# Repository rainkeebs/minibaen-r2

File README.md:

# minibaen
 These files made in KiCad 5.99 (Nightly)
 
 These files are tested but I assume 0 responsibility should something go wrong.
 
 Firmware can be found [here](https://github.com/rainkeebs/vial-qmk/tree/vial/keyboards/minibaen)

Sorry for messy files...

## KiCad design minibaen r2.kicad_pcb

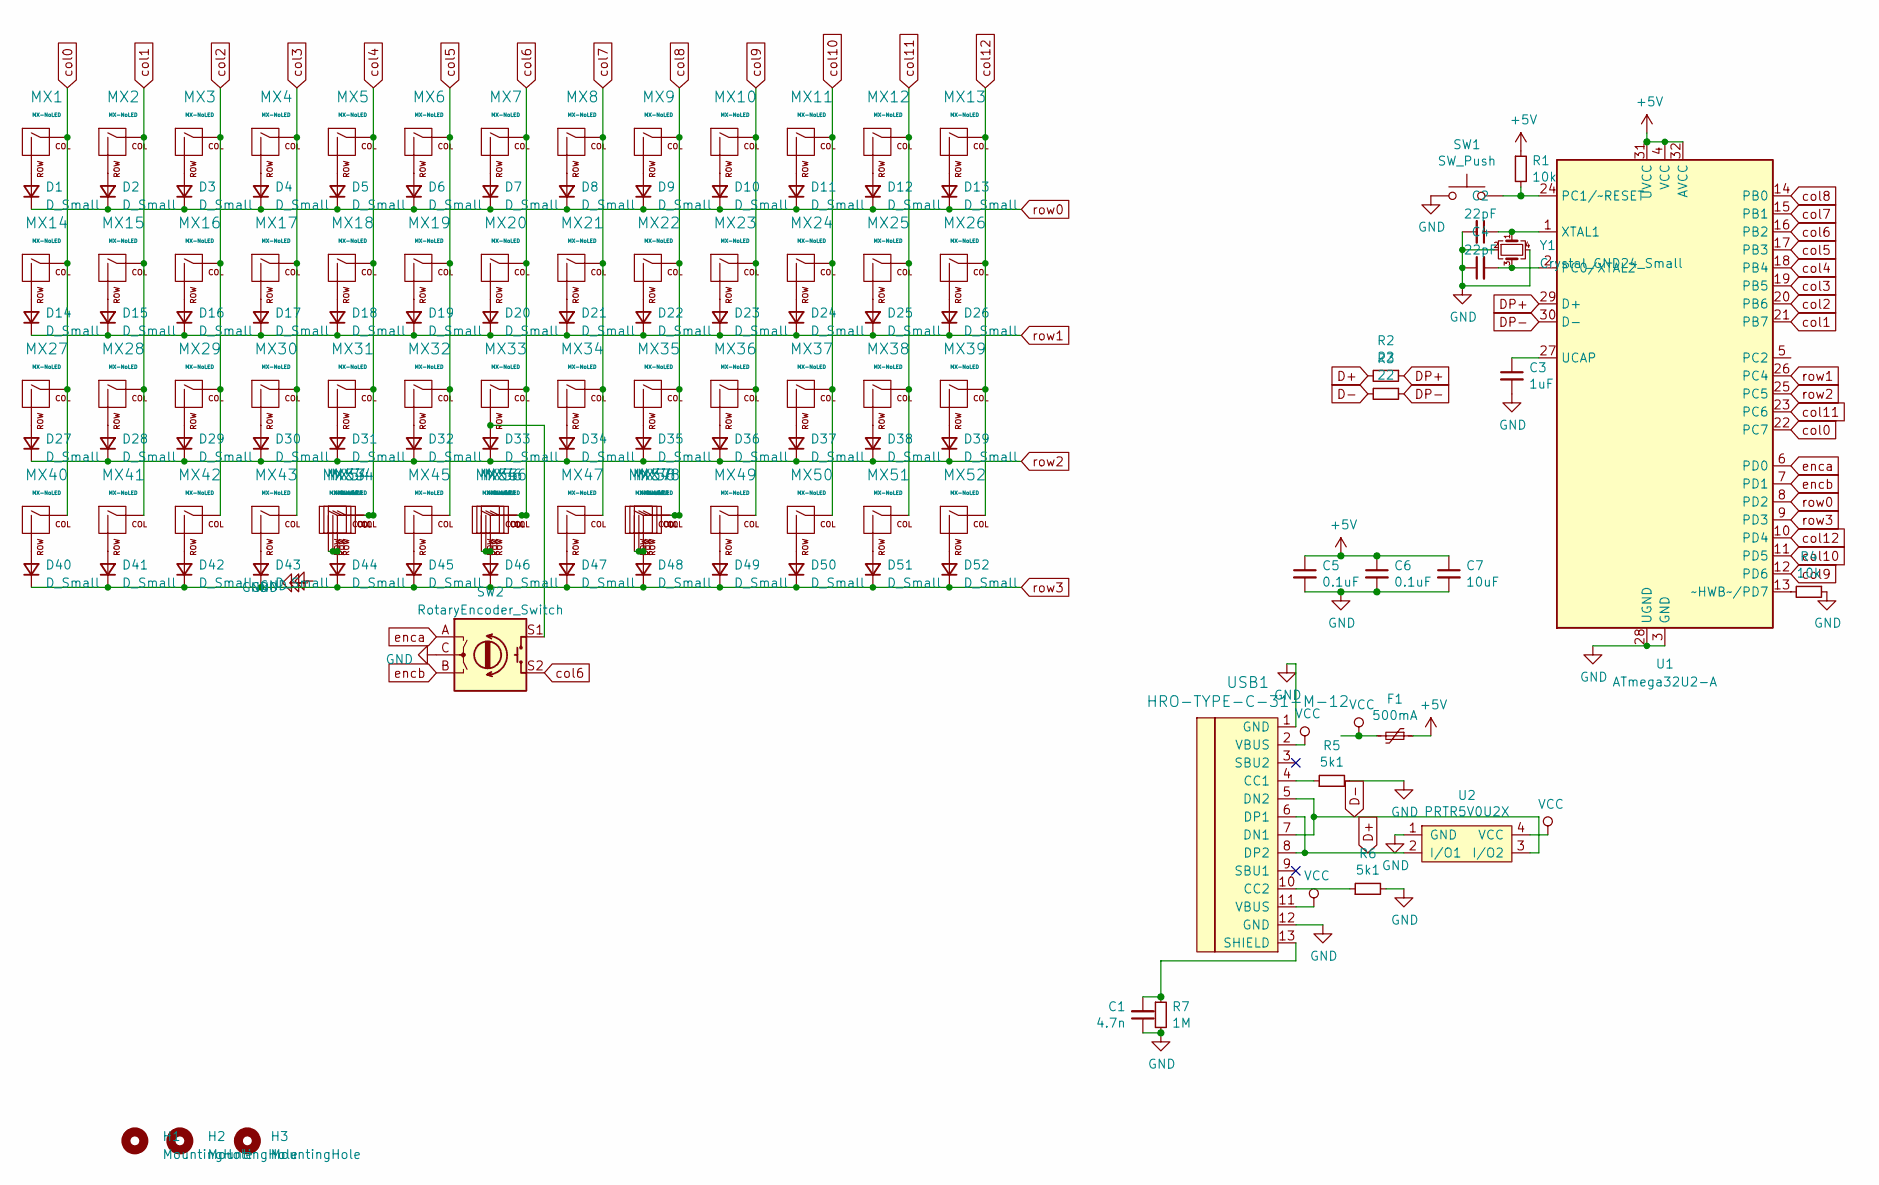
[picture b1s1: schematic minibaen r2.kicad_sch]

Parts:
C1: 4.7n; C_0603_1608Metric
C2, C4: 22pF; C_0603_1608Metric
C3: 1uF; C_0603_1608Metric
C5, C6: 0.1uF; C_0603_1608Metric
C7: 10uF; C_0603_1608Metric
D1, D2, D3, D4, D5, D6, D7, D8, D9, D10, D11, D12, D13, D14, D15, D16, D17, D18, D19, D20, D21, D22, D23, D24, D25, D26, D27, D28, D29, D30, D31, D32, D33, D34, D35, D36, D37, D38, D39, D40, D41, D42, D43, D44, D45, D46, D47, D48, D49, D50, D51, D52: D_Small; D_SOD-123
F1: 500mA; Fuse_1206_3216Metric
H1, H2, H3: MountingHole; MountingHole_2.2mm_M2_DIN965_Pad
MX1, MX2, MX3, MX4, MX5, MX6, MX7, MX8, MX9, MX10, MX11, MX12, MX13, MX14, MX15, MX16, MX17, MX18, MX19, MX20, MX21, MX22, MX23, MX24, MX25, MX26, MX27, MX28, MX29, MX30, MX31, MX32, MX33, MX34, MX35, MX36, MX37, MX38, MX39, MX40, MX41, MX42, MX43, MX44, MX45, MX46, MX47, MX48, MX49, MX50, MX51, MX52: MX-NoLED; MXOnly-1U-NoLED
MX53, MX57: MX-NoLED; MXOnly-2U-ReversedStabilizers-NoLED
MX54, MX56, MX58: MX-NoLED; MXOnly-3U-ReversedStabilizers-NoLED
MX55: MX-NoLED; MXOnly-7U-ReversedStabilizers-NoLED
R1, R4: 10k; R_0603_1608Metric
R2, R3: 22; R_0603_1608Metric
R5, R6: 5k1; R_0603_1608Metric
R7: 1M; R_0603_1608Metric
SW1: SW_Push; PinHeader_1x02_P2.54mm_Vertical
SW2: RotaryEncoder_Switch; RotaryEncoder_EC11-no-legs
U1: ATmega32U2-A; TQFP-32_7x7mm_P0.8mm
U2: PRTR5V0U2X; SOT-143
USB1: HRO-TYPE-C-31-M-12
Y1: Crystal_GND24_Small; Crystal_SMD_3225-4Pin_3.2x2.5mm

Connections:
+5V: C5.1, C6.1, C7.1, F1.1, R1.1, U1.4 (VCC), U1.31 (UVCC), U1.32 (AVCC)
D+: R2.2, U2.2 (I/O1), USB1.6 (DP1), USB1.8 (DP2)
D-: R3.2, U2.3 (I/O2), USB1.5 (DN2), USB1.7 (DN1)
DP+: R2.1, U1.29 (D+)
DP-: R3.1, U1.30 (D-)
GND: C1.1, C2.2, C3.2, C4.1, C5.2, C6.2, C7.2, R4.1, R5.2, R6.2, R7.2, SW1.1, SW2.C, U1.3 (GND), U1.28 (UGND), U2.1 (GND), USB1.1 (GND), USB1.12 (GND), Y1.2, Y1.4
unnamed: C1.2, R7.1, USB1.13 (SHIELD)
unnamed: C2.1, U1.1 (XTAL1), Y1.1
unnamed: C3.1, U1.27 (UCAP)
unnamed: C4.2, U1.2 (PC0/XTAL2), Y1.3
unnamed: D1.2 (A), MX1.2 (ROW)
unnamed: D2.2 (A), MX2.2 (ROW)
unnamed: D3.2 (A), MX3.2 (ROW)
unnamed: D4.2 (A), MX4.2 (ROW)
unnamed: D5.2 (A), MX5.2 (ROW)
unnamed: D6.2 (A), MX6.2 (ROW)
unnamed: D7.2 (A), MX7.2 (ROW)
unnamed: D8.2 (A), MX8.2 (ROW)
unnamed: D9.2 (A), MX9.2 (ROW)
unnamed: D10.2 (A), MX10.2 (ROW)
unnamed: D11.2 (A), MX11.2 (ROW)
unnamed: D12.2 (A), MX12.2 (ROW)
unnamed: D13.2 (A), MX13.2 (ROW)
unnamed: D14.2 (A), MX14.2 (ROW)
unnamed: D15.2 (A), MX15.2 (ROW)
unnamed: D16.2 (A), MX16.2 (ROW)
unnamed: D17.2 (A), MX17.2 (ROW)
unnamed: D18.2 (A), MX18.2 (ROW)
unnamed: D19.2 (A), MX19.2 (ROW)
unnamed: D20.2 (A), MX20.2 (ROW)
unnamed: D21.2 (A), MX21.2 (ROW)
unnamed: D22.2 (A), MX22.2 (ROW)
unnamed: D23.2 (A), MX23.2 (ROW)
unnamed: D24.2 (A), MX24.2 (ROW)
unnamed: D25.2 (A), MX25.2 (ROW)
unnamed: D26.2 (A), MX26.2 (ROW)
unnamed: D27.2 (A), MX27.2 (ROW)
unnamed: D28.2 (A), MX28.2 (ROW)
unnamed: D29.2 (A), MX29.2 (ROW)
unnamed: D30.2 (A), MX30.2 (ROW)
unnamed: D31.2 (A), MX31.2 (ROW)
unnamed: D32.2 (A), MX32.2 (ROW)
unnamed: D33.2 (A), MX33.2 (ROW), SW2.S1
unnamed: D34.2 (A), MX34.2 (ROW)
unnamed: D35.2 (A), MX35.2 (ROW)
unnamed: D36.2 (A), MX36.2 (ROW)
unnamed: D37.2 (A), MX37.2 (ROW)
unnamed: D38.2 (A), MX38.2 (ROW)
unnamed: D39.2 (A), MX39.2 (ROW)
unnamed: D40.2 (A), MX40.2 (ROW)
unnamed: D41.2 (A), MX41.2 (ROW)
unnamed: D42.2 (A), MX42.2 (ROW)
unnamed: D43.2 (A), MX43.2 (ROW)
unnamed: D44.2 (A), MX44.2 (ROW), MX53.2 (ROW), MX54.2 (ROW)
unnamed: D45.2 (A), MX45.2 (ROW)
unnamed: D46.2 (A), MX46.2 (ROW), MX55.2 (ROW), MX56.2 (ROW)
unnamed: D47.2 (A), MX47.2 (ROW)
unnamed: D48.2 (A), MX48.2 (ROW), MX57.2 (ROW), MX58.2 (ROW)
unnamed: D49.2 (A), MX49.2 (ROW)
unnamed: D50.2 (A), MX50.2 (ROW)
unnamed: D51.2 (A), MX51.2 (ROW)
unnamed: D52.2 (A), MX52.2 (ROW)
unnamed: R1.2, SW1.2, U1.24 (PC1/~RESET)
unnamed: R4.2, U1.13 (~HWB~/PD7)
unnamed: R5.1, USB1.4 (CC1)
unnamed: R6.1, USB1.10 (CC2)
VCC: F1.2, U2.4 (VCC), USB1.2 (VBUS), USB1.11 (VBUS)
col0: MX1.1 (COL), MX14.1 (COL), MX27.1 (COL), MX40.1 (COL), U1.22 (PC7)
col1: MX2.1 (COL), MX15.1 (COL), MX28.1 (COL), MX41.1 (COL), U1.21 (PB7)
col2: MX3.1 (COL), MX16.1 (COL), MX29.1 (COL), MX42.1 (COL), U1.20 (PB6)
col3: MX4.1 (COL), MX17.1 (COL), MX30.1 (COL), MX43.1 (COL), U1.19 (PB5)
col4: MX5.1 (COL), MX18.1 (COL), MX31.1 (COL), MX44.1 (COL), MX53.1 (COL), MX54.1 (COL), U1.18 (PB4)
col5: MX6.1 (COL), MX19.1 (COL), MX32.1 (COL), MX45.1 (COL), U1.17 (PB3)
col6: MX7.1 (COL), MX20.1 (COL), MX33.1 (COL), MX46.1 (COL), MX55.1 (COL), MX56.1 (COL), SW2.S2, U1.16 (PB2)
col7: MX8.1 (COL), MX21.1 (COL), MX34.1 (COL), MX47.1 (COL), U1.15 (PB1)
col8: MX9.1 (COL), MX22.1 (COL), MX35.1 (COL), MX48.1 (COL), MX57.1 (COL), MX58.1 (COL), U1.14 (PB0)
col9: MX10.1 (COL), MX23.1 (COL), MX36.1 (COL), MX49.1 (COL), U1.12 (PD6)
col10: MX11.1 (COL), MX24.1 (COL), MX37.1 (COL), MX50.1 (COL), U1.11 (PD5)
col11: MX12.1 (COL), MX25.1 (COL), MX38.1 (COL), MX51.1 (COL), U1.23 (PC6)
col12: MX13.1 (COL), MX26.1 (COL), MX39.1 (COL), MX52.1 (COL), U1.10 (PD4)
enca: SW2.A, U1.6 (PD0)
encb: SW2.B, U1.7 (PD1)
row0: D1.1 (K), D2.1 (K), D3.1 (K), D4.1 (K), D5.1 (K), D6.1 (K), D7.1 (K), D8.1 (K), D9.1 (K), D10.1 (K), D11.1 (K), D12.1 (K), D13.1 (K), U1.8 (PD2)
row1: D14.1 (K), D15.1 (K), D16.1 (K), D17.1 (K), D18.1 (K), D19.1 (K), D20.1 (K), D21.1 (K), D22.1 (K), D23.1 (K), D24.1 (K), D25.1 (K), D26.1 (K), U1.26 (PC4)
row2: D27.1 (K), D28.1 (K), D29.1 (K), D30.1 (K), D31.1 (K), D32.1 (K), D33.1 (K), D34.1 (K), D35.1 (K), D36.1 (K), D37.1 (K), D38.1 (K), D39.1 (K), U1.25 (PC5)
row3: D40.1 (K), D41.1 (K), D42.1 (K), D43.1 (K), D44.1 (K), D45.1 (K), D46.1 (K), D47.1 (K), D48.1 (K), D49.1 (K), D50.1 (K), D51.1 (K), D52.1 (K), U1.9 (PD3)

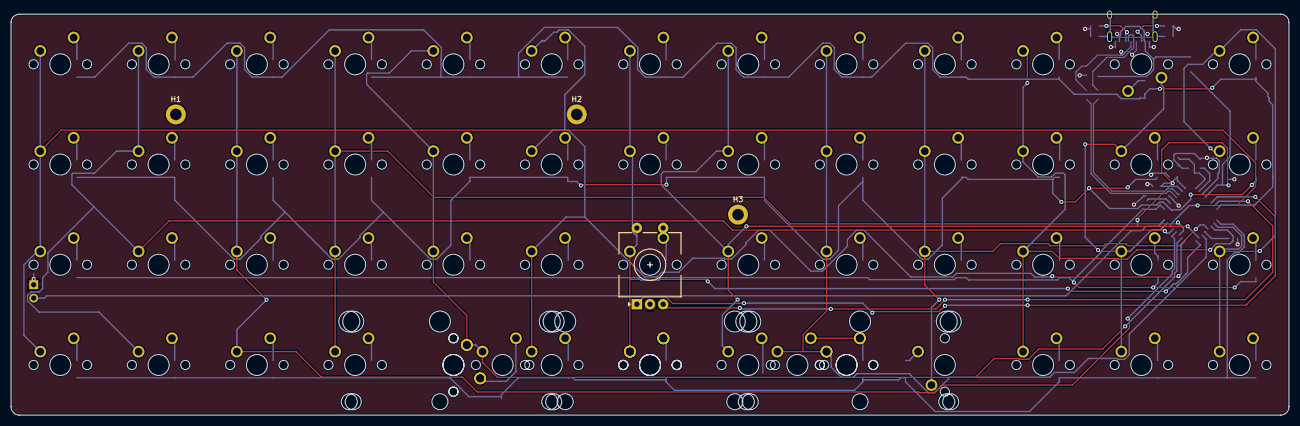
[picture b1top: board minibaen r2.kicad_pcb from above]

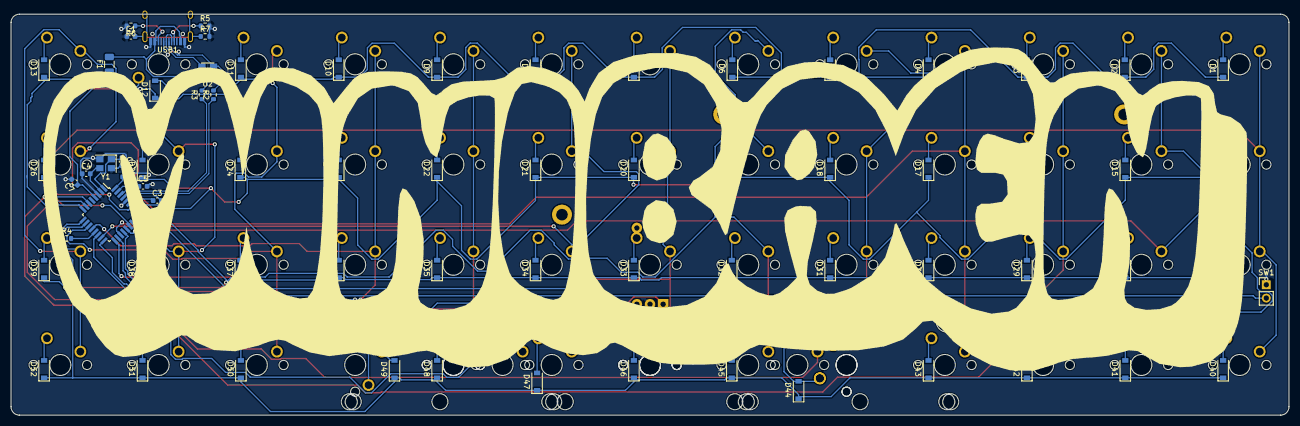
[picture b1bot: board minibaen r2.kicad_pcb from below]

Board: 2 copper layers, 242.9 x 76.2 mm, 134 parts (72 on the bottom side), 86 nets.

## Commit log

2021-09-05 hello!
